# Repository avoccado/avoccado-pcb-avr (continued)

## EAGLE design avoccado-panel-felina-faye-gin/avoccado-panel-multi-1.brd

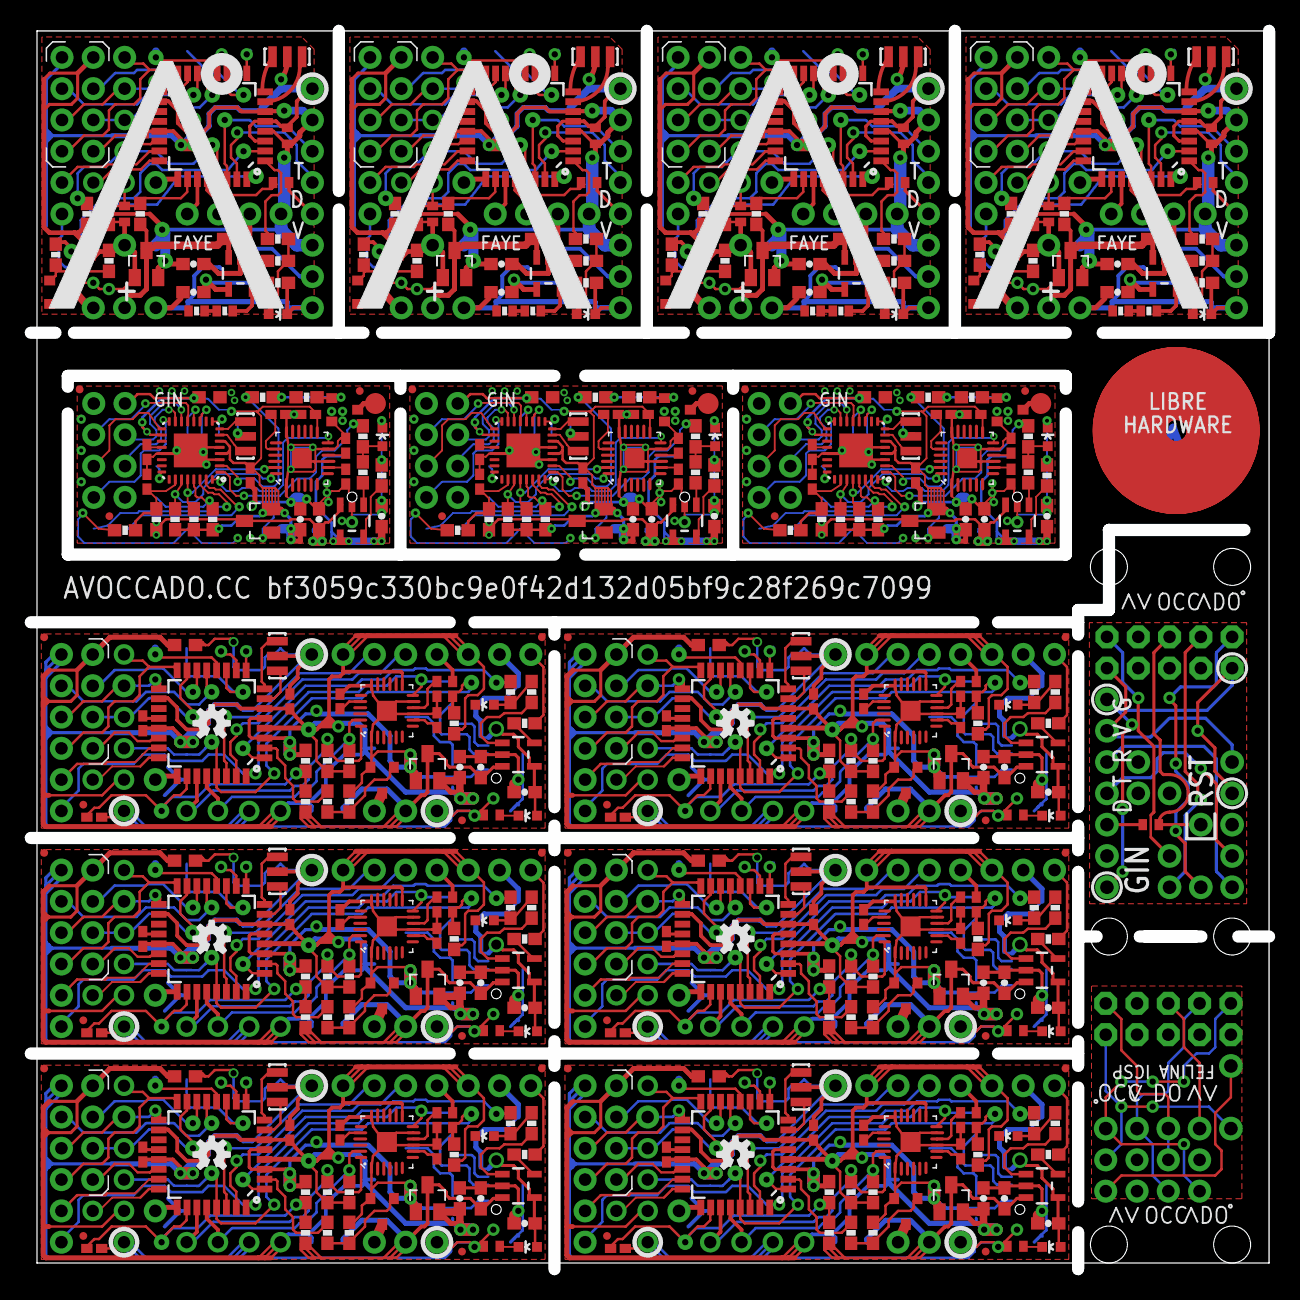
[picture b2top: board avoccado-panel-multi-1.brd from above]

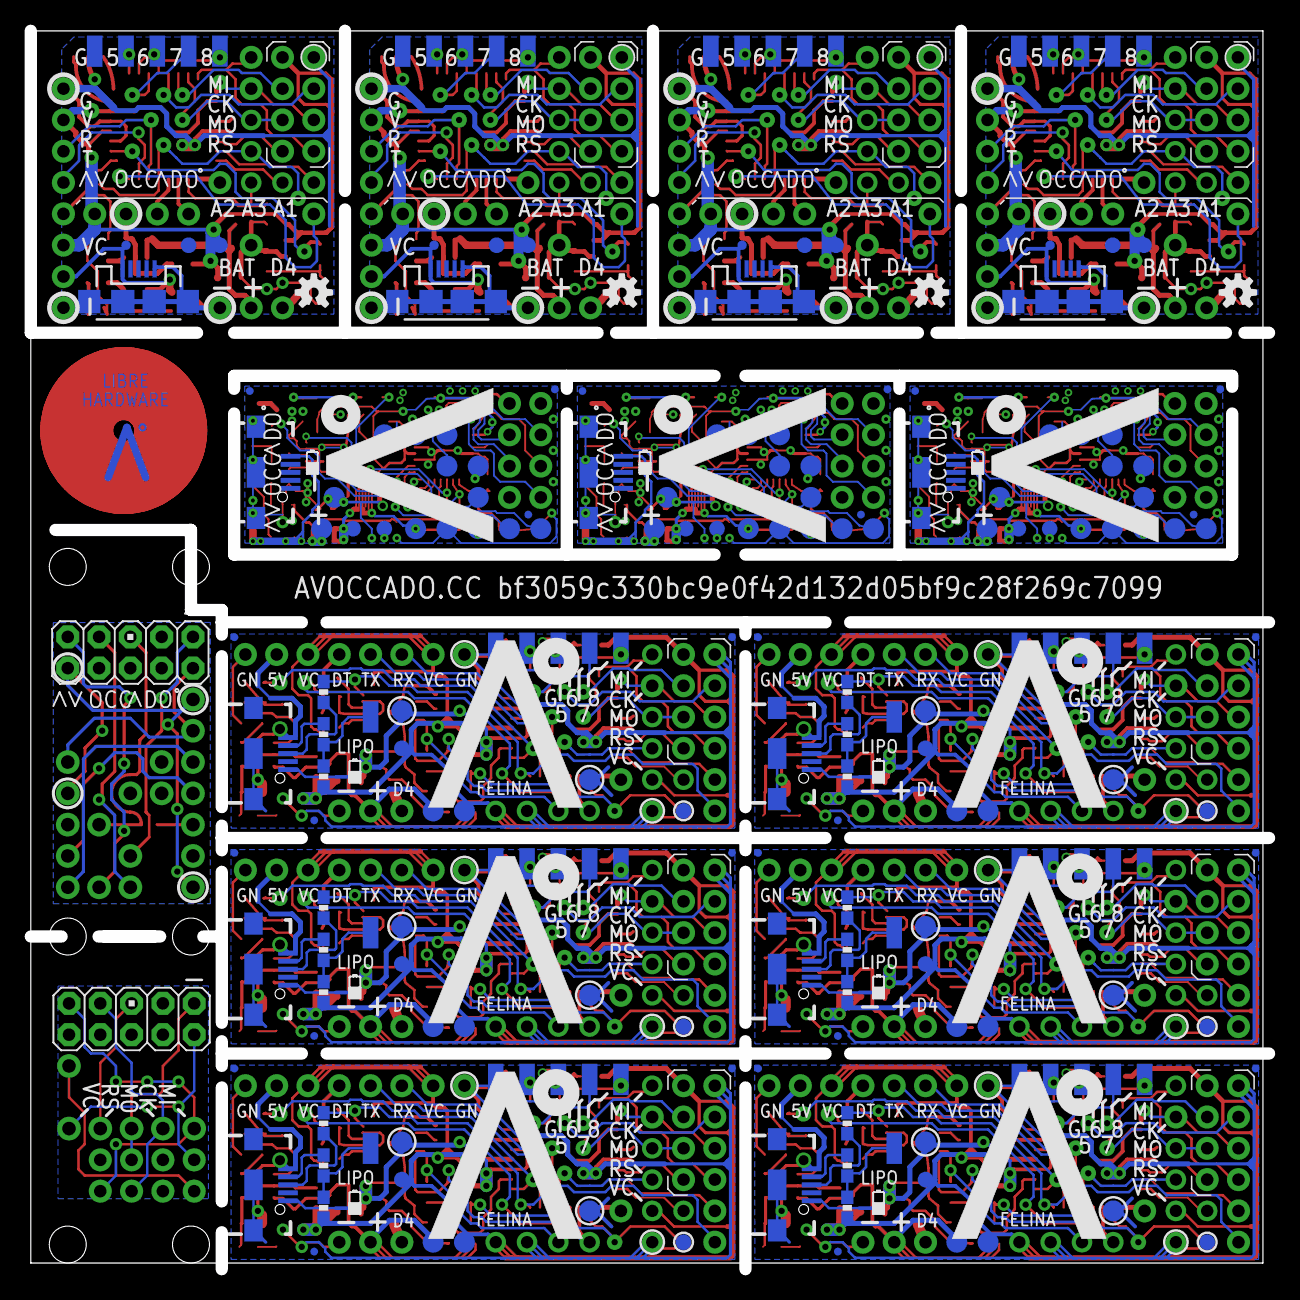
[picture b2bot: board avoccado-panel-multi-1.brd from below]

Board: 2 copper layers, 100.5 x 100.5 mm, 939 parts (213 on the bottom side), 510 nets.

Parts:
C1, C2, C3, C7, C8, C11, C13, C14, C16, C19, C20, C22, C24, C25, C27, C30, C31, C33, C35, C36, C38, C41, C42, C44, C46, C47, C49, C52, C53, C55, C57, C58, C60, C63, C64, C66, C68, C69, C73, C74, C76, C77, C79, C80, C84, C85, C87, C88, C98, C99, C127, C128, C130, C131: 0.1uF; C0402K
C4, C5, C6, C15, C17, C18, C26, C28, C29, C37, C39, C40, C48, C50, C51, C59, C61, C62, C70, C71, C72, C81, C82, C83, C92, C94, C95, C103, C105, C106, C111, C113, C114, C119, C121, C122, C124, C125, C126: 4.7uF; 0603-CAP
C9, C21, C32, C43, C54, C65, C75, C86, C129: 2.2nF; C0402K
C10, C12, C23, C34, C45, C56: 0.1uF; C0603
C67, C78, C97: 4.7uF; C0603
C89, C90, C91, C93, C96, C100, C101, C102, C104, C107, C108, C109, C110, C112, C115, C116, C117, C118, C120, C123: 0.1uF; C0402
C132: C0402
D1, D2, D3, D4, D5, D6, D7, D8, D9, D10, D11, D12, D13, D14, D15, D16, D17, D18, D19: LED; LED-0603
FID1, FID2, FID3, FID4, FID5, FID6, FID7, FID8, FID9, FID10, FID11, FID12, FID13, FID14, FID15, FID16, FID17, FID18, FID19, FID20, FID21, FID22, FID23, FID24, FID25, FID26, FID27, FID28, FID29, FID30, FID31, FID32, FID33, FID34, FID35, FID36, FID37, FID38, FID39, FID40, FID41, FID42, FID43, FID44, FID45, FID46, FID47, FID48, FID49, FID50, FID51, FID52, FID53, FID54, FID55, FID56, FID57, FID58, FID59, FID60: FIDUCIALUFIDUCIAL; MICRO-FIDUCIAL
JP1, JP4, JP5, JP12, JP14, JP15, JP16, JP20, JP30, JP31, JP35, JP37, JP38, JP43, JP52, JP53, JP54, JP55, JP56, JP57, JP64, JP66, JP67, JP72, JP81, JP82, JP83, JP84, JP85, JP86, JP93, JP95, JP96, JP101, JP110, JP111, JP112, JP113, JP114, JP115, JP122, JP124, JP125, JP130, JP139, JP140, JP141, JP142, JP143, JP144, JP151, JP153, JP154, JP159, JP168, JP169, JP170, JP171, JP172, JP173, JP197, JP198, JP203, JP205, JP224, JP225, JP230, JP232, JP251, JP252, JP257, JP259, JP273, JP274, JP279, JP281: M01NOSILK-KIT; 1X01NS-KIT
JP2, JP27, JP28, JP29, JP48, JP49, JP50, JP51, JP77, JP78, JP79, JP80, JP106, JP107, JP108, JP109, JP135, JP136, JP137, JP138, JP164, JP165, JP166, JP167, JP175, JP176, JP177, JP178, JP180, JP181, JP182, JP183, JP210, JP211, JP212, JP213, JP214, JP215, JP237, JP238, JP239, JP240, JP241, JP242, JP264, JP265, JP266, JP267, JP268, JP269, JP286, JP287, JP288, JP289, JP290, JP291, JP293, JP294, JP295, JP296, JP876, JP877, JP878, JP879: M021X02_NO_SILK; 1X02_NO_SILK
JP3, JP6, JP7, JP8, JP9, JP10, JP11, JP13, JP17, JP18, JP19, JP21, JP23, JP24, JP25, JP26, JP32, JP33, JP34, JP36, JP39, JP40, JP41, JP42, JP44, JP45, JP46, JP47, JP59, JP60, JP61, JP62, JP63, JP65, JP68, JP69, JP70, JP71, JP73, JP74, JP75, JP76, JP88, JP89, JP90, JP91, JP92, JP94, JP97, JP98, JP99, JP100, JP102, JP103, JP104, JP105, JP117, JP118, JP119, JP120, JP121, JP123, JP126, JP127, JP128, JP129, JP131, JP132, JP133, JP134, JP146, JP147, JP148, JP149, JP150, JP152, JP155, JP156, JP157, JP158, JP160, JP161, JP162, JP163, JP185, JP186, JP187, JP188, JP189, JP190, JP191, JP192, JP193, JP194, JP195, JP196, JP199, JP200, JP201, JP202, JP204, JP206, JP207, JP208, JP209, JP217, JP218, JP219, JP220, JP221, JP222, JP223, JP226, JP227, JP228, JP229, JP231, JP233, JP234, JP235, JP236, JP244, JP245, JP246, JP247, JP248, JP249, JP250, JP253, JP254, JP255, JP256, JP258, JP260, JP261, JP262, JP263, JP271, JP272, JP275, JP276, JP277, JP278, JP280, JP282, JP283, JP284, JP285: M01PTH; 1X01
JP22, JP58, JP87, JP116, JP145, JP174, JP179, JP184, JP297: USB_MICROB_PLUGCONN-11752; USB-B-MICRO-SMD_V03
JP216, JP243, JP270, JP292: USB-MICROB
LDO, LDO1, LDO2, LDO3, LDO4, LDO5, LDO6, LDO7, LDO8, LDO9, LDO10, LDO11, LDO12: MCP1703CB; SOT23
LOGO1, LOGO2, LOGO3, LOGO4, LOGO5, LOGO6, LOGO7, LOGO8, LOGO9, LOGO10: OSHW-LOGOS; OSHW-LOGO-S
MCU, MCU1, MCU2, MCU3, MCU4, MCU5, MCU6, MCU7, MCU8, MCU9: ATMEGA328P_TQFP; TQFP32-08
Q1, Q3, Q5, Q7, Q9, Q11, Q13, Q15, Q17, Q19, Q21, Q23, Q25: 16MHz; RESONATOR-SMD
Q2, Q4, Q6, Q8, Q10, Q12, Q18, Q20, Q22, Q24: FET; SOT23-3
Q14, Q16, Q26: N-FET; SOT23-3
R1, R6, R16, R20, R30, R34, R44, R48, R58, R62, R72, R76, R86, R90, R96, R100, R106, R110, R116, R120, R126, R130, R136, R140, R146, R150: 511R; 0603-RES
R2, R10, R11, R12, R23, R24, R29, R37, R38, R43, R51, R52, R57, R65, R66, R71, R79, R80, R85, R93, R94, R95, R103, R104, R105, R115, R125, R135, R145, R153, R154: 10K; 0603-RES
R3, R4, R15, R17, R18, R27, R31, R32, R41, R45, R46, R55, R59, R60, R69, R73, R74, R83, R87, R88, R97, R98, R147, R148: 2K; 0603-RES
R5, R7, R8, R19, R21, R22, R33, R35, R36, R47, R49, R50, R61, R63, R64, R75, R77, R78, R89, R91, R92, R99, R101, R102, R109, R111, R112, R119, R121, R122, R129, R131, R132, R139, R141, R142, R149, R151, R152: 4.7M; 0603-RES
R9, R28, R42, R56, R70, R84: 2K; R0402
R13, R14, R25, R26, R39, R40, R53, R54, R67, R68, R81, R82: 68R; 0603-RES
R107, R117, R127, R137: RP; 0603-RES
R108, R118, R128, R138: 1K; 0603-RES
R113, R114, R123, R124, R133, R134, R143, R144: 1K; 0402-RES
TP1, TP6, TP7, TP8, TP9, TP11, TP14, TP15, TP16, TP17, TP21, TP23, TP27, TP28, TP29, TP30, TP34, TP36, TP40, TP41, TP42, TP43, TP47, TP49, TP53, TP54, TP55, TP56, TP60, TP62, TP66, TP67, TP68, TP69, TP73, TP75, TP111, TP112, TP113, TP114, TP119, TP127, TP128, TP129, TP130, TP135, TP136, TP137, TP138, TP139, TP144, TP145, TP146, TP147, TP148, TP153: TEST-POINT2; PAD.02X.02
TP2, TP18, TP31, TP44, TP57, TP70, TP115, TP131, TP140, TP149: M01PTH; 1X01
TP3, TP5, TP19, TP20, TP32, TP33, TP45, TP46, TP58, TP59, TP71, TP72, TP79, TP80, TP95, TP96, TP116, TP117, TP120, TP121, TP132, TP133, TP141, TP142, TP150, TP151: TEST-POINT3X5; PAD.03X.05
TP4, TP10, TP12, TP13, TP22, TP24, TP25, TP26, TP35, TP37, TP38, TP39, TP48, TP50, TP51, TP52, TP61, TP63, TP64, TP65, TP74, TP76, TP77, TP78, TP81, TP82, TP83, TP84, TP85, TP86, TP87, TP88, TP89, TP90, TP91, TP92, TP93, TP94, TP97, TP98, TP99, TP100, TP101, TP102, TP103, TP104, TP105, TP106, TP107, TP108, TP109, TP110, TP122, TP123, TP124, TP125, TP126, TP154, TP155, TP156, TP157, TP158, TP159, TP160, TP161, TP162: TPTP20R; TP20R
TP118, TP134, TP143, TP152: TEST-POINT3; PAD.03X.03
TP163, TP164, TP165, TP166, TP167, TP168, TP169, TP170, TP171, TP172, TP173, TP174, TP175, TP176, TP177, TP178, TP179, TP180, TP181, TP559, TP560, TP561, TP562, TP563, TP564: PTR1PAD1-13; P1-13
U1, U4, U6, U8, U10, U12, U14, U17, U21: MPU-6000QFN-24; QFN-24-TESTING
U2, U3, U5, U7, U9, U11, U13, U16, U19, U20, U22, U23, U24: MCP73831; SOT23-5
U15, U18, U25: MLF32-PAD
U$1, U$6: AVR_SPI_PROG; AVR_ICSP

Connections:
3.3V: C3.2, C6.1, C10.1, JP1.1, JP2.2, JP4.1, JP11.1, JP18.1, LDO.2, MCU.4, MCU.6, MCU.18, R2.2, R10.2, R11.2, R15.2, TP5.P$1, TP13.TP, U1.13
3.3V1: C12.1, C13.2, C18.1, JP34.1, JP41.1, JP48.2, JP52.1, JP56.1, LDO1.2, MCU1.4, MCU1.6, MCU1.18, R12.2, R23.2, R24.2, R27.2, TP19.P$1, TP25.TP, U4.13
3.3V2: C23.1, C24.2, C29.1, JP63.1, JP70.1, JP77.2, JP81.1, JP85.1, LDO2.2, MCU2.4, MCU2.6, MCU2.18, R29.2, R37.2, R38.2, R41.2, TP32.P$1, TP38.TP, U6.13
3.3V3: C34.1, C35.2, C40.1, JP92.1, JP99.1, JP106.2, JP110.1, JP114.1, LDO3.2, MCU3.4, MCU3.6, MCU3.18, R43.2, R51.2, R52.2, R55.2, TP45.P$1, TP51.TP, U8.13
3.3V4: C45.1, C46.2, C51.1, JP121.1, JP128.1, JP135.2, JP139.1, JP143.1, LDO4.2, MCU4.4, MCU4.6, MCU4.18, R57.2, R65.2, R66.2, R69.2, TP58.P$1, TP64.TP, U10.13
3.3V5: C56.1, C57.2, C62.1, JP150.1, JP157.1, JP164.2, JP168.1, JP172.1, LDO5.2, MCU5.4, MCU5.6, MCU5.18, R71.2, R79.2, R80.2, R83.2, TP71.P$1, TP77.TP, U12.13
3.3V6: C67.1, C68.2, C72.1, C77.2, JP175.2, LDO6.2, R85.2, R93.2, R94.2, TP79.P$1, TP89.TP, U14.13, U15.4, U15.6, U15.18
3.3V7: C78.1, C79.2, C83.1, C88.2, JP180.2, LDO7.2, R95.2, R103.2, R104.2, TP95.P$1, TP105.TP, U17.13, U18.4, U18.6, U18.18
3.3V8: C89.1, C90.2, C95.1, JP189.1, JP277.1, JP286.2, JP290.1, LDO8.2, MCU9.4, MCU9.6, MCU9.18, R105.2, TP116.P$1
3.3V9: C100.1, C101.2, C106.1, JP194.1, JP201.1, JP210.2, JP214.1, LDO9.2, MCU6.4, MCU6.6, MCU6.18, R115.2, TP132.P$1
3.3V10: C108.1, C109.2, C114.1, JP221.1, JP228.1, JP237.2, JP241.1, LDO10.2, MCU7.4, MCU7.6, MCU7.18, R125.2, TP141.P$1
3.3V11: C116.1, C117.2, C122.1, JP248.1, JP255.1, JP264.2, JP268.1, LDO11.2, MCU8.4, MCU8.6, MCU8.18, R135.2, TP150.P$1
3.3V12: C97.1, C98.2, C126.1, C131.2, JP293.2, LDO12.2, R145.2, R153.2, R154.2, TP120.P$1, TP157.TP, U21.13, U25.4, U25.6, U25.18
3.3V13: TP169.TP, TP175.TP, TP180.TP, U$1.2
3.3V44: JP876.2, TP560.TP, U$6.2
5V: C4.1, D2.A, JP17.1, JP22.VBUS1, U2.4
5V1: C15.1, D4.A, JP40.1, JP58.VBUS1, U3.4
5V2: C26.1, D6.A, JP69.1, JP87.VBUS1, U5.4
5V3: C37.1, D8.A, JP98.1, JP116.VBUS1, U7.4
5V4: C48.1, D10.A, JP127.1, JP145.VBUS1, U9.4
5V5: C59.1, D12.A, JP156.1, JP174.VBUS1, U11.4
5V6: C70.1, JP179.VBUS1, U13.4
5V7: C81.1, JP184.VBUS1, U16.4
5V8: C92.1, JP276.1, JP292.VBUS, TP118.P$1, U19.4
5V9: C103.1, JP200.1, JP216.VBUS, TP134.P$1, U22.4
5V10: C111.1, JP227.1, JP243.VBUS, TP143.P$1, U23.4
5V11: C119.1, JP254.1, JP270.VBUS, TP152.P$1, U24.4
5V12: C124.1, JP297.VBUS1, U20.4
7-TO-D-: R14.1, R15.1, TP11.P$1
7-TO-D-1: R26.1, R27.1, TP23.P$1
7-TO-D-2: R40.1, R41.1, TP36.P$1
7-TO-D-3: R54.1, R55.1, TP49.P$1
7-TO-D-4: R68.1, R69.1, TP62.P$1
7-TO-D-5: R82.1, R83.1, TP75.P$1
A0: JP19.1, MCU.23
A1: JP20.1, MCU.24
A2: JP21.1, MCU.25
A3: C7.1, MCU.26, R7.2, R8.1
A4: JP31.1, MCU.27, R11.1, U1.24
A5: JP30.1, MCU.28, R10.1, U1.23
A7: JP54.1, MCU1.28, R23.1, U4.23
A7-NRF-IRQ: JP29.2, MCU.22
A7-NRF-IRQ1: JP51.2, MCU1.22
A7-NRF-IRQ2: JP80.2, MCU2.22
A7-NRF-IRQ3: JP109.2, MCU3.22
A7-NRF-IRQ4: JP138.2, MCU4.22
A7-NRF-IRQ5: JP167.2, MCU5.22
A7-NRF-IRQ8: JP289.2, MCU9.22
A7-NRF-IRQ9: JP213.2, MCU6.22
A7-NRF-IRQ10: JP240.2, MCU7.22
A7-NRF-IRQ11: JP267.2, MCU8.22
A8: JP55.1, MCU1.27, R24.1, U4.24
A9: C19.1, MCU1.26, R21.2, R22.1
A10: JP44.1, MCU1.25
A11: JP43.1, MCU1.24
A12: JP42.1, MCU1.23
A14: JP83.1, MCU2.28, R37.1, U6.23
A15: JP84.1, MCU2.27, R38.1, U6.24
A16: C30.1, MCU2.26, R35.2, R36.1
A17: JP73.1, MCU2.25
A18: JP72.1, MCU2.24
A19: JP71.1, MCU2.23
A21: JP112.1, MCU3.28, R51.1, U8.23
A22: JP113.1, MCU3.27, R52.1, U8.24
A23: C41.1, MCU3.26, R49.2, R50.1
A24: JP102.1, MCU3.25
A25: JP101.1, MCU3.24
A26: JP100.1, MCU3.23
A28: JP141.1, MCU4.28, R65.1, U10.23
A29: JP142.1, MCU4.27, R66.1, U10.24
A30: C52.1, MCU4.26, R63.2, R64.1
A31: JP131.1, MCU4.25
A32: JP130.1, MCU4.24
A33: JP129.1, MCU4.23
A35: JP170.1, MCU5.28, R79.1, U12.23
A36: JP171.1, MCU5.27, R80.1, U12.24
A37: C63.1, MCU5.26, R77.2, R78.1
A38: JP160.1, MCU5.25
A39: JP159.1, MCU5.24
A40: JP158.1, MCU5.23
A42: R93.1, U14.23, U15.28
A43: R94.1, U14.24, U15.27
A44: C73.1, R91.2, R92.1, U15.26
A46: TP88.TP, U15.24
A49: R103.1, U17.23, U18.28
A50: R104.1, U17.24, U18.27
A51: C84.1, R101.2, R102.1, U18.26
A53: TP104.TP, U18.24
A56: JP291.1, MCU9.28
A57: JP291.2, MCU9.27
A58: C96.1, JP281.1, MCU9.26, R111.2, R112.1
A59: JP280.1, MCU9.25
A60: JP279.1, MCU9.24
A61: JP278.1, MCU9.23
A63: JP215.1, MCU6.28
A64: JP215.2, MCU6.27
A65: C107.1, JP205.1, MCU6.26, R121.2, R122.1
A66: JP204.1, MCU6.25
A67: JP203.1, MCU6.24
A68: JP202.1, MCU6.23
A70: JP242.1, MCU7.28
A71: JP242.2, MCU7.27
A72: C115.1, JP232.1, MCU7.26, R131.2, R132.1
A73: JP231.1, MCU7.25
A74: JP230.1, MCU7.24
A75: JP229.1, MCU7.23
A77: JP269.1, MCU8.28
A78: JP269.2, MCU8.27
A79: C123.1, JP259.1, MCU8.26, R141.2, R142.1
A80: JP258.1, MCU8.25
A81: JP257.1, MCU8.24
A82: JP256.1, MCU8.23
A84: R153.1, U21.23, U25.28
A85: R154.1, U21.24, U25.27
A86: C127.1, R151.2, R152.1, U25.26
A88: TP156.TP, U25.24
AREF: C1.2, MCU.20
AREF1: C14.2, MCU1.20
AREF2: C25.2, MCU2.20
AREF3: C36.2, MCU3.20
AREF4: C47.2, MCU4.20
AREF5: C58.2, MCU5.20
AREF6: C69.2, U15.20
AREF7: C80.2, U18.20
AREF8: C91.2, MCU9.20
AREF9: C102.2, MCU6.20
AREF10: C110.2, MCU7.20
AREF11: C118.2, MCU8.20
AREF12: C99.2, U25.20
CHG-PROG: R3.2, U2.5
CHG-PROG1: R17.2, U3.5
CHG-PROG2: R31.2, U5.5
CHG-PROG3: R45.2, U7.5
CHG-PROG4: R59.2, U9.5
CHG-PROG5: R73.2, U11.5
CHG-PROG6: R87.2, U13.5
CHG-PROG7: R97.2, U16.5
CHG-PROG8: R107.2, R113.2, U19.5
CHG-PROG9: R117.2, R123.2, U22.5
CHG-PROG10: R127.2, R133.2, U23.5
CHG-PROG11: R137.2, R143.2, U24.5
CHG-PROG12: R147.2, U20.5
D1: JP49.1, MCU1.13
D2: MCU1.12, TP17.P$1
D2-INT: MCU.32, R13.1, TP2.1, U1.12
D2-INT1: MCU1.32, R25.1, TP18.1, U4.12
D2-INT2: MCU2.32, R39.1, TP31.1, U6.12
D2-INT3: MCU3.32, R53.1, TP44.1, U8.12
D2-INT4: MCU4.32, R67.1, TP57.1, U10.12
D2-INT5: MCU5.32, R81.1, TP70.1, U12.12
D2-INT6: U14.12, U15.32
D2-INT7: U17.12, U18.32
D2-INT8: U21.12, U25.32
D3: MCU.1, R6.1
D4: MCU.2, R1.1
D5: MCU.9, TP1.P$1
D6: MCU.10, TP6.P$1
D7: MCU.11, TP7.P$1
D8: MCU.12, TP8.P$1
D9: JP27.1, MCU.13
D10: JP27.2, MCU.14
D11: MCU1.1, R20.1
D12: MCU1.2, R16.1
D13: MCU1.9, TP14.P$1
D14: MCU1.10, TP15.P$1
D15: MCU1.11, TP16.P$1
D16: JP49.2, MCU1.14
D17: JP78.1, MCU2.13
D18: MCU2.12, TP30.P$1
D19: MCU2.1, R34.1
D20: MCU2.2, R30.1
D21: MCU2.9, TP27.P$1
D22: MCU2.10, TP28.P$1
D23: MCU2.11, TP29.P$1
D24: JP78.2, MCU2.14
D25: JP107.1, MCU3.13
D26: MCU3.12, TP43.P$1
D27: MCU3.1, R48.1
D28: MCU3.2, R44.1
D29: MCU3.9, TP40.P$1
D30: MCU3.10, TP41.P$1
D31: MCU3.11, TP42.P$1
D32: JP107.2, MCU3.14
D33: JP136.1, MCU4.13
D34: MCU4.12, TP56.P$1
D35: MCU4.1, R62.1
D36: MCU4.2, R58.1
D37: MCU4.9, TP53.P$1
D38: MCU4.10, TP54.P$1
D39: MCU4.11, TP55.P$1
D40: JP136.2, MCU4.14
D41: JP165.1, MCU5.13
D42: MCU5.12, TP69.P$1
D43: MCU5.1, R76.1
D44: MCU5.2, R72.1
D45: MCU5.9, TP66.P$1
D46: MCU5.10, TP67.P$1
D47: MCU5.11, TP68.P$1
D48: JP165.2, MCU5.14
D49: JP176.1, U15.13
D50: TP90.TP, U15.12
D51: R90.1, U15.1
D52: R86.1, U15.2
D53: TP92.TP, U15.9
D55: TP91.TP, U15.11
D56: JP176.2, U15.14
D57: JP181.1, U18.13
D58: TP106.TP, U18.12
D59: R100.1, U18.1
D60: R96.1, U18.2
D61: TP108.TP, U18.9
D63: TP107.TP, U18.11
D64: JP181.2, U18.14
D65: JP287.1, MCU9.13
D66: MCU9.12, TP114.P$1
D67: MCU9.32, TP115.1
D68: MCU9.1, R110.1
D69: MCU9.2, R106.1
D70: MCU9.9, TP111.P$1
D71: MCU9.10, TP112.P$1
D72: MCU9.11, TP113.P$1
D73: JP211.1, MCU6.13
D74: MCU6.12, TP130.P$1
D75: MCU6.32, TP131.1
D76: MCU6.1, R120.1
D77: MCU6.2, R116.1
D78: MCU6.9, TP127.P$1
D79: MCU6.10, TP128.P$1
D80: MCU6.11, TP129.P$1
D81: JP211.2, MCU6.14
D82: JP238.1, MCU7.13
D83: MCU7.12, TP139.P$1
D84: MCU7.32, TP140.1
D85: MCU7.1, R130.1
D86: MCU7.2, R126.1
D87: MCU7.9, TP136.P$1
D88: MCU7.10, TP137.P$1
D89: MCU7.11, TP138.P$1
D90: JP238.2, MCU7.14
D91: JP265.1, MCU8.13
D92: MCU8.12, TP148.P$1
D93: MCU8.32, TP149.1
D94: MCU8.1, R140.1
D95: MCU8.2, R136.1
D96: MCU8.9, TP145.P$1
D97: MCU8.10, TP146.P$1
D98: MCU8.11, TP147.P$1
D99: JP265.2, MCU8.14
D100: JP287.2, MCU9.14
D101: JP294.1, U25.13
D102: TP158.TP, U25.12
D103: R150.1, U25.1
D104: R146.1, U25.2
D105: TP160.TP, U25.9
D107: TP159.TP, U25.11
D108: JP294.2, U25.14
DTR: C2.2, JP10.1
DTR1: C16.2, JP33.1
DTR2: C27.2, JP62.1
DTR3: C38.2, JP91.1
DTR4: C49.2, JP120.1
DTR5: C60.2, JP149.1
DTR6: C104.2, JP193.1
DTR7: C112.2, JP220.1
DTR8: C120.2, JP247.1
DTR9: C93.2, JP188.1
DTR29: C132.2, TP172.TP
GND: C1.1, C3.1, C4.2, C5.2, C6.2, C7.2, C8.2, C9.2, C10.2, C11.2, D1.C, JP2.1, JP3.1, JP5.1, JP6.1, JP16.1, JP22.GND1, JP22.SHIELD1, JP22.SHIELD2, JP22.SHIELD3, JP25.1, LDO.1, MCU.3, MCU.5, MCU.21, Q1.2, Q2.2, R3.1, R5.1, R7.1, R9.1, TP3.P$1, TP4.TP, TP9.P$1, TP12.TP, U1.1, U1.9, U1.11, U1.18, U2.2
GND1: C12.2, C13.1, C14.1, C15.2, C17.2, C18.2, C19.2, C20.2, C21.2, C22.2, D3.C, JP7.1, JP39.1, JP47.1, JP48.1, JP53.1, JP57.1, JP58.GND1, JP58.SHIELD1, JP58.SHIELD2, JP58.SHIELD3, LDO1.1, MCU1.3, MCU1.5, MCU1.21, Q3.2, Q4.2, R17.1, R19.1, R21.1, R28.1, TP20.P$1, TP21.P$1, TP24.TP, TP26.TP, U3.2, U4.1, U4.9, U4.11, U4.18
GND2: C23.2, C24.1, C25.1, C26.2, C28.2, C29.2, C30.2, C31.2, C32.2, C33.2, D5.C, JP59.1, JP68.1, JP76.1, JP77.1, JP82.1, JP86.1, JP87.GND1, JP87.SHIELD1, JP87.SHIELD2, JP87.SHIELD3, LDO2.1, MCU2.3, MCU2.5, MCU2.21, Q5.2, Q6.2, R31.1, R33.1, R35.1, R42.1, TP33.P$1, TP34.P$1, TP37.TP, TP39.TP, U5.2, U6.1, U6.9, U6.11, U6.18
GND3: C34.2, C35.1, C36.1, C37.2, C39.2, C40.2, C41.2, C42.2, C43.2, C44.2, D7.C, JP88.1, JP97.1, JP105.1, JP106.1, JP111.1, JP115.1, JP116.GND1, JP116.SHIELD1, JP116.SHIELD2, JP116.SHIELD3, LDO3.1, MCU3.3, MCU3.5, MCU3.21, Q7.2, Q8.2, R45.1, R47.1, R49.1, R56.1, TP46.P$1, TP47.P$1, TP50.TP, TP52.TP, U7.2, U8.1, U8.9, U8.11, U8.18
GND4: C45.2, C46.1, C47.1, C48.2, C50.2, C51.2, C52.2, C53.2, C54.2, C55.2, D9.C, JP117.1, JP126.1, JP134.1, JP135.1, JP140.1, JP144.1, JP145.GND1, JP145.SHIELD1, JP145.SHIELD2, JP145.SHIELD3, LDO4.1, MCU4.3, MCU4.5, MCU4.21, Q9.2, Q10.2, R59.1, R61.1, R63.1, R70.1, TP59.P$1, TP60.P$1, TP63.TP, TP65.TP, U9.2, U10.1, U10.9, U10.11, U10.18
GND5: C56.2, C57.1, C58.1, C59.2, C61.2, C62.2, C63.2, C64.2, C65.2, C66.2, D11.C, JP146.1, JP155.1, JP163.1, JP164.1, JP169.1, JP173.1, JP174.GND1, JP174.SHIELD1, JP174.SHIELD2, JP174.SHIELD3, LDO5.1, MCU5.3, MCU5.5, MCU5.21, Q11.2, Q12.2, R73.1, R75.1, R77.1, R84.1, TP72.P$1, TP73.P$1, TP76.TP, TP78.TP, U11.2, U12.1, U12.9, U12.11, U12.18
GND6: C67.2, C68.1, C69.1, C70.2, C71.2, C72.2, C73.2, C74.2, C75.2, C76.2, C77.1, D13.C, JP175.1, JP179.GND1, JP179.SHIELD1, JP179.SHIELD2, JP179.SHIELD3, LDO6.1, Q13.2, Q14.2, R87.1, R89.1, R91.1, TP80.P$1, TP82.TP, TP93.TP, TP94.TP, U13.2, U14.1, U14.9, U14.11, U14.18, U15.3, U15.5, U15.21, U15.PAD
GND7: C78.2, C79.1, C80.1, C81.2, C82.2, C83.2, C84.2, C85.2, C86.2, C87.2, C88.1, D14.C, JP180.1, JP184.GND1, JP184.SHIELD1, JP184.SHIELD2, JP184.SHIELD3, LDO7.1, Q15.2, Q16.2, R97.1, R99.1, R101.1, TP96.P$1, TP98.TP, TP109.TP, TP110.TP, U16.2, U17.1, U17.9, U17.11, U17.18, U18.3, U18.5, U18.21, U18.PAD
GND8: C89.2, C90.1, C91.1, C92.2, C94.2, C95.2, C96.2, D15.C, JP185.1, JP275.1, JP284.1, JP285.1, JP286.1, JP290.2, JP292.GND, JP292.MT1, JP292.MT2, LDO8.1, MCU9.3, MCU9.5, MCU9.21, Q17.2, Q18.2, R107.1, R109.1, R111.1, R114.1, TP117.P$1, TP119.P$1, U19.2
GND9: C100.2, C101.1, C102.1, C103.2, C105.2, C106.2, C107.2, D16.C, JP190.1, JP199.1, JP208.1, JP209.1, JP210.1, JP214.2, JP216.GND, JP216.MT1, JP216.MT2, LDO9.1, MCU6.3, MCU6.5, MCU6.21, Q19.2, Q20.2, R117.1, R119.1, R121.1, R124.1, TP133.P$1, TP135.P$1, U22.2
GND10: C108.2, C109.1, C110.1, C111.2, C113.2, C114.2, C115.2, D17.C, JP217.1, JP226.1, JP235.1, JP236.1, JP237.1, JP241.2, JP243.GND, JP243.MT1, JP243.MT2, LDO10.1, MCU7.3, MCU7.5, MCU7.21, Q21.2, Q22.2, R127.1, R129.1, R131.1, R134.1, TP142.P$1, TP144.P$1, U23.2
GND11: C116.2, C117.1, C118.1, C119.2, C121.2, C122.2, C123.2, D18.C, JP244.1, JP253.1, JP262.1, JP263.1, JP264.1, JP268.2, JP270.GND, JP270.MT1, JP270.MT2, LDO11.1, MCU8.3, MCU8.5, MCU8.21, Q23.2, Q24.2, R137.1, R139.1, R141.1, R144.1, TP151.P$1, TP153.P$1, U24.2
GND12: C97.2, C98.1, C99.1, C124.2, C125.2, C126.2, C127.2, C128.2, C129.2, C130.2, C131.1, D19.C, JP293.1, JP297.GND1, JP297.SHIELD1, JP297.SHIELD2, JP297.SHIELD3, LDO12.1, Q25.2, Q26.2, R147.1, R149.1, R151.1, TP121.P$1, TP123.TP, TP161.TP, TP162.TP, U20.2, U21.1, U21.9, U21.11, U21.18, U25.3, U25.5, U25.21, U25.PAD
GND13: TP170.TP, TP176.TP, TP181.TP, U$1.10
GND44: JP876.1, TP559.TP, U$6.10
LED: D1.A, R4.1, R6.2
LED1: D3.A, R18.1, R20.2
LED2: D5.A, R32.1, R34.2
LED3: D7.A, R46.1, R48.2
LED4: D9.A, R60.1, R62.2
LED5: D11.A, R74.1, R76.2
LED6: D13.A, R88.1, R90.2
LED7: D14.A, R98.1, R100.2
LED8: D15.A, R108.1, R110.2
LED9: D16.A, R118.1, R120.2
LED10: D17.A, R128.1, R130.2
LED11: D18.A, R138.1, R140.2
LED12: D19.A, R148.1, R150.2
MISO: JP12.1, JP29.1, MCU.16
MISO1: JP35.1, JP51.1, MCU1.16
MISO2: JP64.1, JP80.1, MCU2.16
MISO3: JP93.1, JP109.1, MCU3.16
MISO4: JP122.1, JP138.1, MCU4.16
MISO5: JP151.1, JP167.1, MCU5.16
MISO6: JP178.1, U15.16
MISO7: JP183.1, U18.16
MISO8: JP271.1, JP289.1, MCU9.16
MISO9: JP195.1, JP213.1, MCU6.16
MISO10: JP222.1, JP240.1, MCU7.16
MISO11: JP249.1, JP267.1, MCU8.16
MISO12: JP296.1, U25.16
MISO13: TP179.TP, U$1.9
MISO44: JP879.1, TP563.TP, U$6.9
MOSI: JP14.1, JP28.2, MCU.15
MOSI1: JP37.1, JP50.2, MCU1.15
MOSI2: JP66.1, JP79.2, MCU2.15
MOSI3: JP95.1, JP108.2, MCU3.15
MOSI4: JP124.1, JP137.2, MCU4.15
MOSI5: JP153.1, JP166.2, MCU5.15
MOSI6: JP177.2, U15.15
MOSI7: JP182.2, U18.15
MOSI8: JP273.1, JP288.2, MCU9.15
MOSI9: JP197.1, JP212.2, MCU6.15
MOSI10: JP224.1, JP239.2, MCU7.15
MOSI11: JP251.1, JP266.2, MCU8.15
MOSI12: JP295.2, U25.15
MOSI13: TP177.TP, U$1.1
MOSI44: JP878.2, TP561.TP, U$6.1
unnamed: MCU.8, Q1.1
unnamed: MCU.7, Q1.3
unnamed: D2.C, R9.2
unnamed: JP22.D+1, R13.2
unnamed: JP22.D-1, R14.2
unnamed: Q2.1, R1.2, R5.2
unnamed: C8.1, U1.10
unnamed: C9.1, U1.20
unnamed: MCU1.8, Q3.1
unnamed: C11.1, U1.8
unnamed: MCU1.7, Q3.3
unnamed: Q4.1, R16.2, R19.2
unnamed: C20.1, U4.10
unnamed: C21.1, U4.20
unnamed: C22.1, U4.8
unnamed: JP58.D+1, R25.2
unnamed: JP58.D-1, R26.2
unnamed: D4.C, R28.2
unnamed: MCU2.8, Q5.1
unnamed: MCU2.7, Q5.3
unnamed: Q6.1, R30.2, R33.2
unnamed: C31.1, U6.10
unnamed: C32.1, U6.20
unnamed: C33.1, U6.8
unnamed: JP87.D+1, R39.2
unnamed: JP87.D-1, R40.2
unnamed: D6.C, R42.2
unnamed: MCU3.8, Q7.1
unnamed: MCU3.7, Q7.3
unnamed: Q8.1, R44.2, R47.2
unnamed: C42.1, U8.10
unnamed: C43.1, U8.20
unnamed: C44.1, U8.8
unnamed: JP116.D+1, R53.2
unnamed: JP116.D-1, R54.2
unnamed: D8.C, R56.2
unnamed: MCU4.8, Q9.1
unnamed: MCU4.7, Q9.3
unnamed: Q10.1, R58.2, R61.2
unnamed: C53.1, U10.10
unnamed: C54.1, U10.20
unnamed: C55.1, U10.8
unnamed: JP145.D+1, R67.2
unnamed: JP145.D-1, R68.2
unnamed: D10.C, R70.2
unnamed: MCU5.8, Q11.1
unnamed: MCU5.7, Q11.3
unnamed: Q12.1, R72.2, R75.2
unnamed: C64.1, U12.10
unnamed: C65.1, U12.20
unnamed: C66.1, U12.8
unnamed: JP174.D+1, R81.2
unnamed: JP174.D-1, R82.2
unnamed: D12.C, R84.2
unnamed: Q13.1, U15.8
unnamed: Q13.3, U15.7
unnamed: Q14.1, R86.2, R89.2
unnamed: C74.1, U14.10
unnamed: C75.1, U14.20
unnamed: C76.1, U14.8
unnamed: Q15.1, U18.8
unnamed: Q15.3, U18.7
unnamed: Q16.1, R96.2, R99.2
unnamed: C85.1, U17.10
unnamed: C86.1, U17.20
unnamed: C87.1, U17.8
unnamed: MCU9.8, Q17.1
unnamed: MCU9.7, Q17.3
unnamed: Q18.1, R106.2, R109.2
unnamed: R113.1, R114.2
unnamed: Q25.1, U25.8
unnamed: Q25.3, U25.7
unnamed: MCU6.8, Q19.1
unnamed: MCU6.7, Q19.3
unnamed: Q20.1, R116.2, R119.2
unnamed: R123.1, R124.2
unnamed: MCU7.8, Q21.1
unnamed: MCU7.7, Q21.3
unnamed: Q22.1, R126.2, R129.2
unnamed: R133.1, R134.2
unnamed: MCU8.8, Q23.1
unnamed: MCU8.7, Q23.3
unnamed: Q24.1, R136.2, R139.2
unnamed: R143.1, R144.2
unnamed: Q26.1, R146.2, R149.2
unnamed: C128.1, U21.10
unnamed: C129.1, U21.20
unnamed: C130.1, U21.8
RESET: C2.1, JP15.1, MCU.29, R2.1
RESET1: C16.1, JP38.1, MCU1.29, R12.1
RESET2: C27.1, JP67.1, MCU2.29, R29.1
RESET3: C38.1, JP96.1, MCU3.29, R43.1
RESET4: C49.1, JP125.1, MCU4.29, R57.1
RESET5: C60.1, JP154.1, MCU5.29, R71.1
RESET6: R85.1, TP87.TP, U15.29
RESET7: R95.1, TP103.TP, U18.29
RESET8: C93.1, JP274.1, MCU9.29, R105.1
RESET9: C104.1, JP198.1, MCU6.29, R115.1
RESET10: C112.1, JP225.1, MCU7.29, R125.1
RESET11: C120.1, JP252.1, MCU8.29, R135.1
RESET12: R145.1, TP155.TP, U25.29
RESET13: C132.1, TP166.TP, U$1.5
RESET44: TP564.TP, U$6.5
RXI: JP8.1, MCU.30
RXI1: JP26.1, MCU1.30
RXI2: JP60.1, MCU2.30
RXI3: JP89.1, MCU3.30
RXI4: JP118.1, MCU4.30
RXI5: JP147.1, MCU5.30
RXI6: TP85.TP, U15.30
RXI7: TP101.TP, U18.30
RXI8: JP186.1, MCU9.30
RXI9: JP191.1, MCU6.30
RXI10: JP218.1, MCU7.30
RXI11: JP245.1, MCU8.30
RXI12: TP126.TP, U25.30
RXI13: TP167.TP, TP173.TP
SCK: JP13.1, JP28.1, MCU.17
SCK1: JP36.1, JP50.1, MCU1.17
SCK2: JP65.1, JP79.1, MCU2.17
SCK3: JP94.1, JP108.1, MCU3.17
SCK4: JP123.1, JP137.1, MCU4.17
SCK5: JP152.1, JP166.1, MCU5.17
SCK6: JP177.1, U15.17
SCK7: JP182.1, U18.17
SCK8: JP272.1, JP288.1, MCU9.17
SCK9: JP196.1, JP212.1, MCU6.17
SCK10: JP223.1, JP239.1, MCU7.17
SCK11: JP250.1, JP266.1, MCU8.17
SCK12: JP295.1, U25.17
SCK13: TP178.TP, U$1.7
SCK44: JP878.1, TP562.TP, U$6.7
SOC: R4.2, U2.1
SOC1: R18.2, U3.1
SOC2: R32.2, U5.1
SOC3: R46.2, U7.1
SOC4: R60.2, U9.1
SOC5: R74.2, U11.1
SOC6: R88.2, U13.1
SOC7: R98.2, U16.1
SOC8: R108.2, U19.1
SOC9: R118.2, U22.1
SOC10: R128.2, U23.1
SOC11: R138.2, U24.1
SOC12: R148.2, U20.1
TXO: JP9.1, MCU.31
TXO1: JP32.1, MCU1.31
TXO2: JP61.1, MCU2.31
TXO3: JP90.1, MCU3.31
TXO4: JP119.1, MCU4.31
TXO5: JP148.1, MCU5.31
TXO6: TP86.TP, U15.31
TXO7: TP102.TP, U18.31
TXO8: JP187.1, MCU9.31
TXO9: JP192.1, MCU6.31
TXO10: JP219.1, MCU7.31
TXO11: JP246.1, MCU8.31
TXO12: TP154.TP, U25.31
TXO13: TP168.TP, TP174.TP
VBAT: C5.1, JP24.1, LDO.3, R8.2, TP10.TP, U2.3
VBAT1: C17.1, JP45.1, LDO1.3, R22.2, TP22.TP, U3.3
VBAT2: C28.1, JP74.1, LDO2.3, R36.2, TP35.TP, U5.3
VBAT3: C39.1, JP103.1, LDO3.3, R50.2, TP48.TP, U7.3
VBAT4: C50.1, JP132.1, LDO4.3, R64.2, TP61.TP, U9.3
VBAT5: C61.1, JP161.1, LDO5.3, R78.2, TP74.TP, U11.3
VBAT6: C71.1, LDO6.3, R92.2, TP81.TP, TP83.TP, U13.3
VBAT7: C82.1, LDO7.3, R102.2, TP97.TP, TP99.TP, U16.3
VBAT8: C94.1, JP282.1, LDO8.3, R112.2, U19.3
VBAT9: C105.1, JP206.1, LDO9.3, R122.2, U22.3
VBAT10: C113.1, JP233.1, LDO10.3, R132.2, U23.3
VBAT11: C121.1, JP260.1, LDO11.3, R142.2, U24.3
VBAT12: C125.1, LDO12.3, R152.2, TP122.TP, TP124.TP, U20.3
VIBR: JP23.1, Q2.3
VIBR1: JP46.1, Q4.3
VIBR2: JP75.1, Q6.3
VIBR3: JP104.1, Q8.3
VIBR4: JP133.1, Q10.3
VIBR5: JP162.1, Q12.3
VIBR6: Q14.3, TP84.TP
VIBR7: Q16.3, TP100.TP
VIBR8: JP283.1, Q18.3
VIBR9: JP207.1, Q20.3
VIBR10: JP234.1, Q22.3
VIBR11: JP261.1, Q24.3
VIBR12: Q26.3, TP125.TP

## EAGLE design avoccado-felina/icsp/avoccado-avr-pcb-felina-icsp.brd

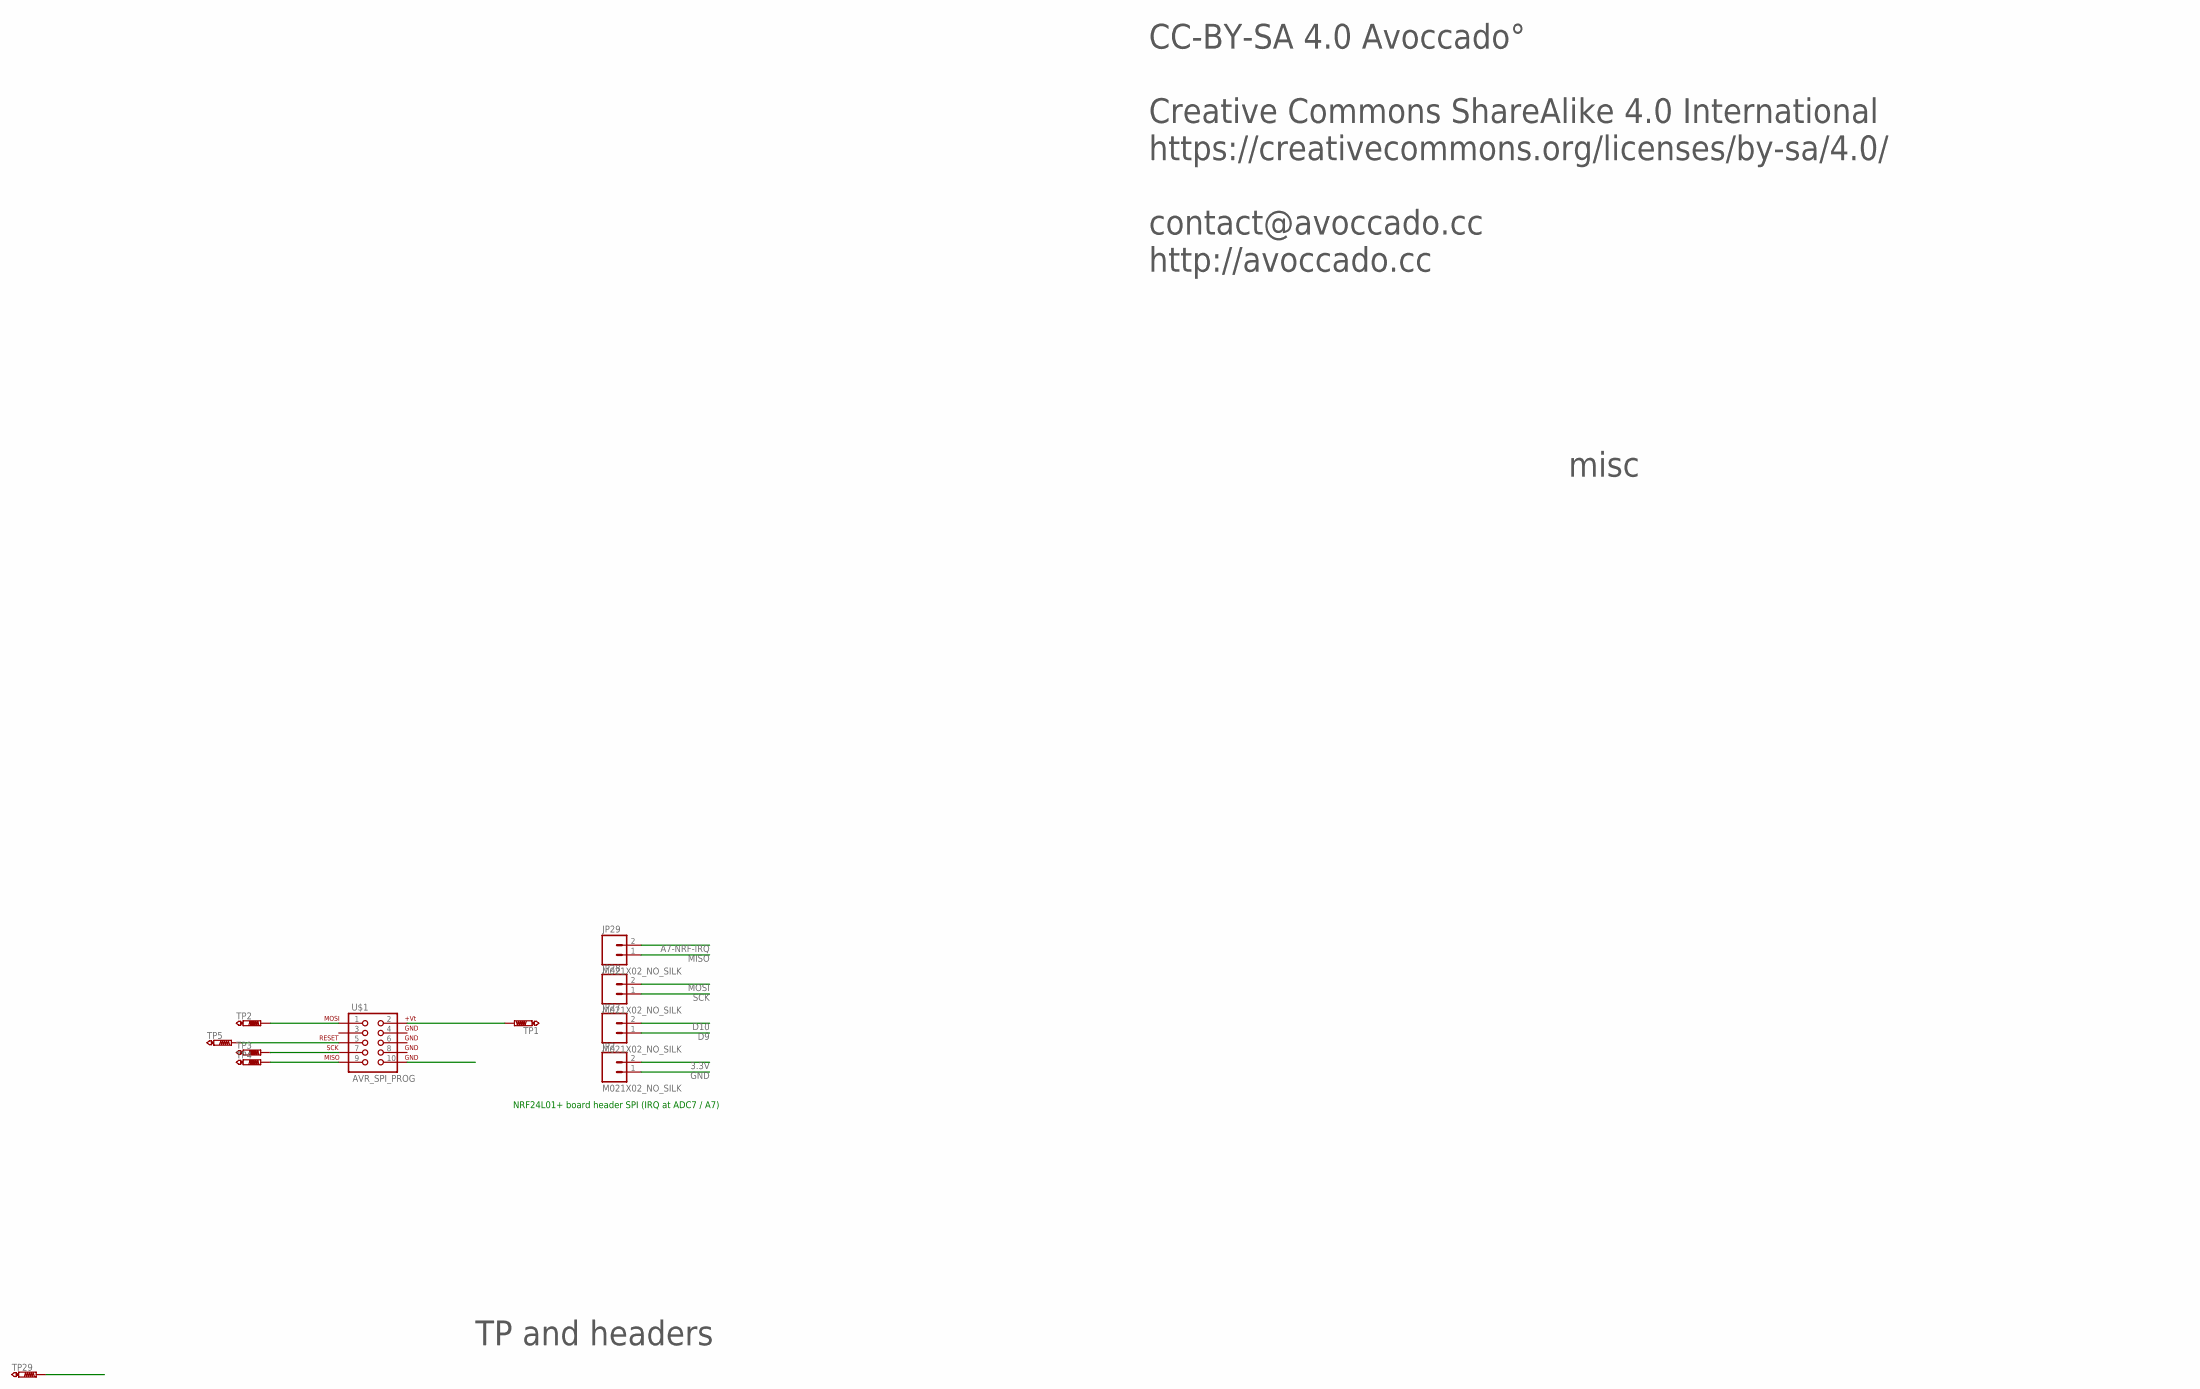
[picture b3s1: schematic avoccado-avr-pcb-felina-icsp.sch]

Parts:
JP2, JP27, JP28, JP29: M021X02_NO_SILK; 1X02_NO_SILK
TP1, TP2, TP3, TP4, TP5, TP29: PTR1PAD1-13; P1-13
U$1: AVR_SPI_PROG; AVR_ICSP

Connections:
3.3V: JP2.2, TP1.TP, U$1.2
A7-NRF-IRQ: JP29.2
D9: JP27.1
D10: JP27.2
GND: JP2.1, TP29.TP, U$1.10
MISO: JP29.1, TP4.TP, U$1.9
MOSI: JP28.2, TP2.TP, U$1.1
RESET: TP5.TP, U$1.5
SCK: JP28.1, TP3.TP, U$1.7

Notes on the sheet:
NRF24L01+ board header SPI (IRQ at ADC7 / A7)
TP and headers
misc
CC-BY-SA 4.0 Avoccado° Creative Commons ShareAlike 4.0 International https://creativecommons.org/licenses/by-sa/4.0/ contact@avoccado.cc http://avoccado.cc

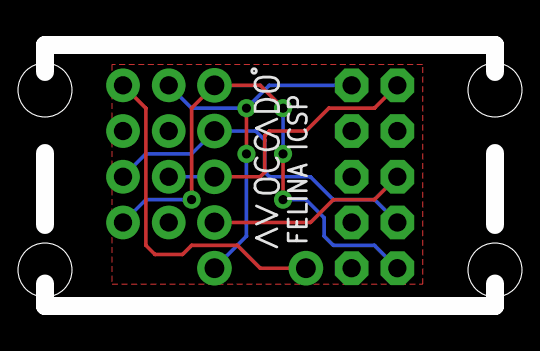
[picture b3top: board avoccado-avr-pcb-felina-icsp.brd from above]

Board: 2 copper layers, 25.0 x 14.5 mm, 11 parts (1 on the bottom side), 6 nets.
